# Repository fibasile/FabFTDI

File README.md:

# FabFTDI
Fabbable FTDI Breakout

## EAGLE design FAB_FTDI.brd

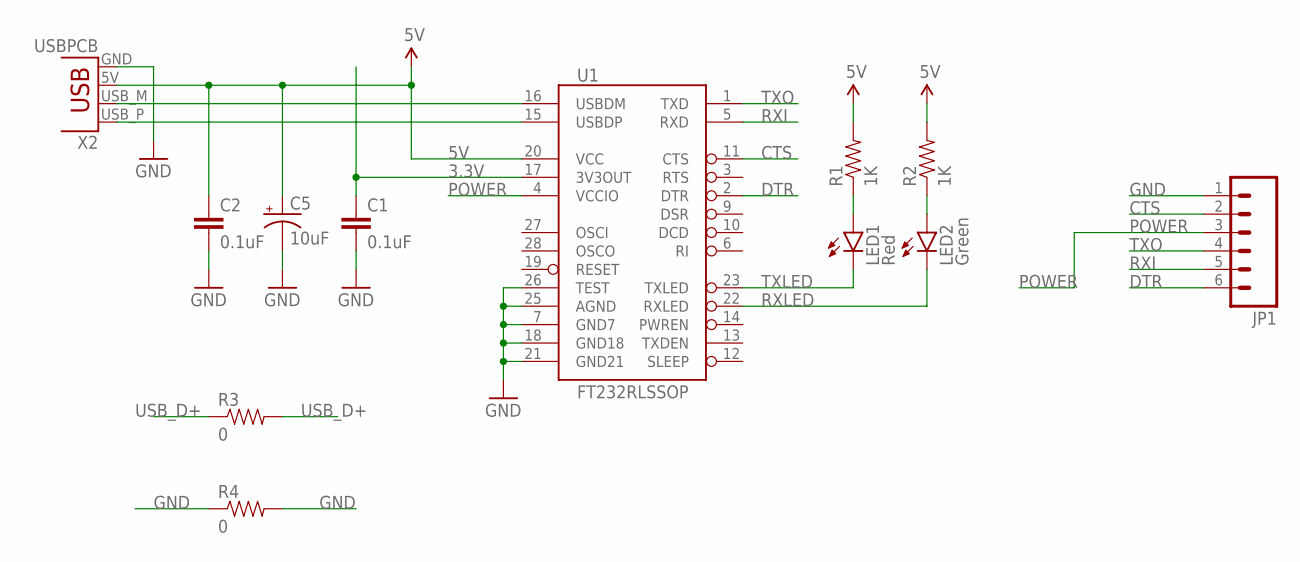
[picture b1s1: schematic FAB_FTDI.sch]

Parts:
C1, C2: 0.1uF; 1206
C5: 10uF; EIA3216
JP1: M06SMD-FEMALE-V2; 1X06-SMD-FEMALE-V2
LED1: Red; LED-1206
LED2: Green; LED-1206
R1, R2: 1K; 1206
R3, R4: 0; 1206
U1: FT232RLSSOP; SSOP28DB
X2: USBPCB; USB-A-PCB

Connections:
3.3V: C1.1, U1.17 (3V3OUT)
5V: C2.1, C5.A (+), R1.2, R2.2, U1.20 (VCC), X2.5V (VBUS)
CTS: JP1.2, U1.11 (CTS)
DTR: JP1.6, U1.2 (DTR)
GND: C1.2, C2.2, C5.C (-), JP1.1, R4.1, R4.2, U1.7 (GND7), U1.18 (GND18), U1.21 (GND21), U1.25 (AGND), U1.26 (TEST), X2.GND
unnamed: LED1.A, R1.1
unnamed: LED2.A, R2.1
POWER: JP1.3, U1.4 (VCCIO)
RXI: JP1.5, U1.5 (RXD)
RXLED: LED2.C, U1.22 (RXLED)
TXLED: LED1.C, U1.23 (TXLED)
TXO: JP1.4, U1.1 (TXD)
USB_D+: R3.1, R3.2, U1.15 (USBDP), X2.USB_P (D+)
USB_D-: U1.16 (USBDM), X2.USB_M (D-)

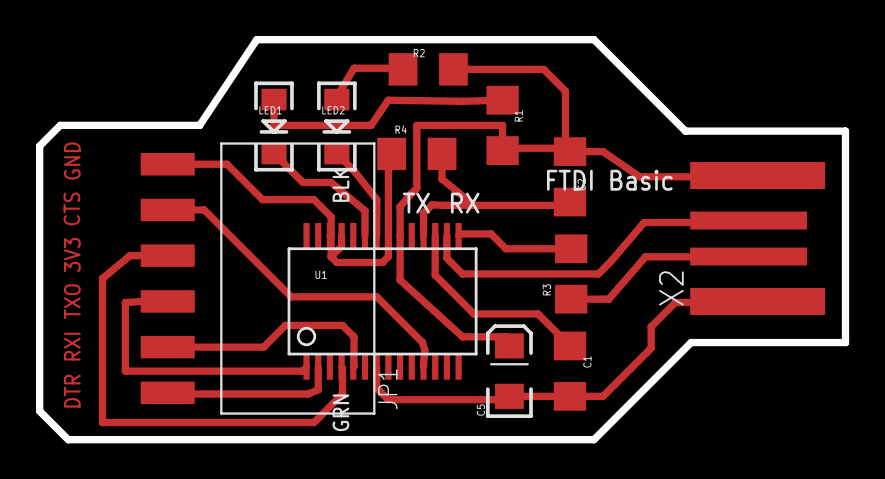
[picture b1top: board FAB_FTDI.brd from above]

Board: 2 copper layers, 44.8 x 22.2 mm, 12 parts (0 on the bottom side), 14 nets.

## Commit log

2017-03-14 Added some images
2017-03-14 Adding Eagle Sources

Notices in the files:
parts and their libraries:
SparkFun-Resistors: Licensing: Creative Commons ShareAlike 4.0 International - https://creativecommons.org/licenses/by-sa/4.0
